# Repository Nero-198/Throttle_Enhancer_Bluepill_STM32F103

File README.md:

# Throttle Enhancer Bluepill STM32F103

## 概要
本プロジェクトは、STM32F103（Bluepill）を用いたスロットルエンハンサーのKiCad設計データです。

## 特徴
- STM32F103（Bluepill）を使用
- KiCad 9.0.3形式の設計ファイル
- ガーバーデータ同梱

HIDデバイスとして動作し、Saitek X-55 throttleにおける不便な機能・存在しない機能の追加を目的としています。

## ファイル構成
- `Throttle_Enhancer_Bluepill_STM32F103.kicad_pcb` : 基板レイアウト
- `Throttle_Enhancer_Bluepill_STM32F103.kicad_sch` : 回路図
- `Throttle_Enhancer_Bluepill_STM32F103.kicad_pro` : プロジェクトファイル
- `V1.zip` : ガーバーデータのZIPアーカイブ

## 使い方
1. KiCad 9.0.3以降でプロジェクトファイルを開く
2. 必要に応じて編集
3. `V1/`内のガーバーデータを基板製造業者に提出

## 必要なソフトウェア
- KiCad 9.0.3以降

## ライセンス
MIT

---

## STM32F103C6Tx ピン配置図

### 主なピンアサイン

| ピン名   | 機能                |
|----------|---------------------|
| PB9      | TDC_CALIBRATION     |
| PB8      | SLIDER_UP           |
| PB7      | SLIDER_HALF_UP      |
| PB6      | SLIDER_PUSH         |
| PB5      | SLIDER_HALF_DOWN    |
| PB4      | SLIDER_DOWN         |
| PA15     | SYS_JTDI            |
| PA14     | SYS_JTCK-SWCLK      |
| PA13     | SYS_JTMS-SWDIO      |
| PA12     | USB_DP              |
| PA11     | USB_DM              |
| PA10     | USART1_RX           |
| PA9      | USART1_TX           |
| PB15     | PINKY_AFT           |
| PB14     | PINKY_FWD           |
| PB13     | DOGFIGHT            |
| PB12     | MISSILE             |
| PA3      | TDC2_Y              |
| PA2      | TDC2_X              |
| PA1      | TDC_Y               |
| PA0      | TDC_X               |
| PA6      | TDC2_PUSH           |
| PA5      | TDC_PUSH            |
| PB1      | BRK_RET             |
| PB0      | BRK_EXT             |

※詳細は画像を参照してください。

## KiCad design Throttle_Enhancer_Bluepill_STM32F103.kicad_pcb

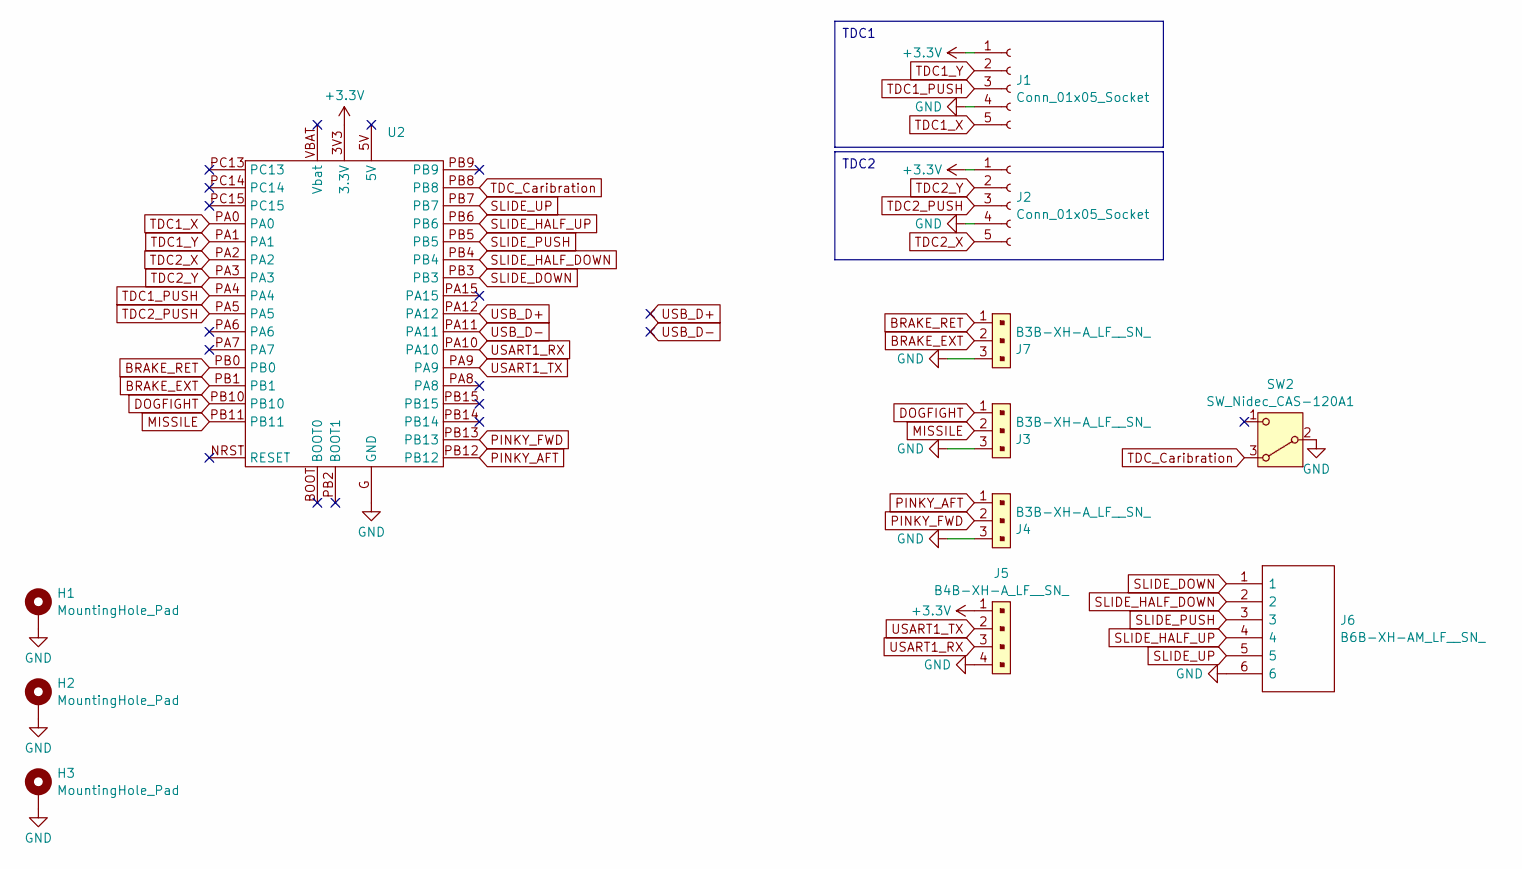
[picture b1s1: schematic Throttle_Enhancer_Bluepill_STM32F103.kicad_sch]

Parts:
H1, H2, H3: MountingHole_Pad; MountingHole_3.2mm_M3_DIN965
J1, J2: Conn_01x05_Socket; PinSocket_1x05_P2.54mm_Vertical
J3, J4, J7: B3B-XH-A_LF__SN_; PinHeader_1x3_P2.5mm_Drill1.1mm; MPN B3B-XH-A(LF)(SN); Digi-Key_PN 455-2248-ND
J5: B4B-XH-A_LF__SN_; PinHeader_1x4_P2.5mm_Drill1.1mm; MPN B4B-XH-A(LF)(SN); Digi-Key_PN 455-2249-ND
J6: B6B-XH-AM_LF__SN_; B6BXHAMLFSN; Manufacturer_Part_Number B6B-XH-AM(LF)(SN)
SW2: SW_Nidec_CAS-120A1; PinSocket_1x03_P2.54mm_Vertical
U2: blue_pill_STM32F103C6T6

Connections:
+3.3V: J1.1, J2.1, J5.1, U2.3V3 (3.3V)
BRAKE_EXT: J7.2, U2.PB1
BRAKE_RET: J7.1, U2.PB0
DOGFIGHT: J3.1, U2.PB10
GND: H1.1, H2.1, H3.1, J1.4, J2.4, J3.3, J4.3, J5.4, J6.6, J7.3, SW2.2 (B), U2.G (GND)
MISSILE: J3.2, U2.PB11
PINKY_AFT: J4.1, U2.PB12
PINKY_FWD: J4.2, U2.PB13
SLIDE_DOWN: J6.1, U2.PB3
SLIDE_HALF_DOWN: J6.2, U2.PB4
SLIDE_HALF_UP: J6.4, U2.PB6
SLIDE_PUSH: J6.3, U2.PB5
SLIDE_UP: J6.5, U2.PB7
TDC1_PUSH: J1.3, U2.PA4
TDC1_X: J1.5, U2.PA0
TDC1_Y: J1.2, U2.PA1
TDC2_PUSH: J2.3, U2.PA5
TDC2_X: J2.5, U2.PA2
TDC2_Y: J2.2, U2.PA3
TDC_Caribration: SW2.3 (A), U2.PB8
USART1_RX: J5.3, U2.PA10
USART1_TX: J5.2, U2.PA9
USB_D+: U2.PA12
USB_D-: U2.PA11

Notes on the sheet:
TDC2
TDC1

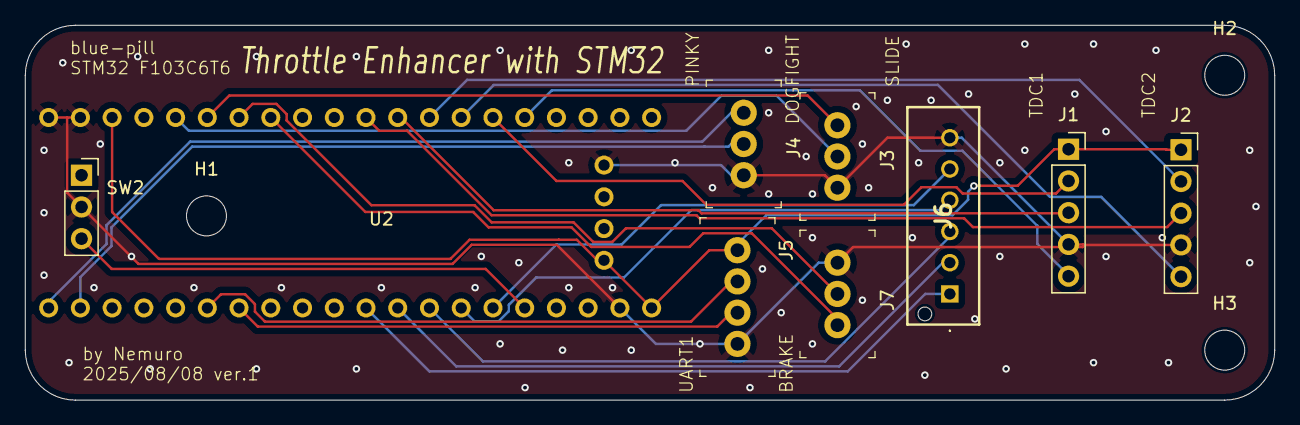
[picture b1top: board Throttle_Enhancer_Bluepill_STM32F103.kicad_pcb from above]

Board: 2 copper layers, 100.0 x 30.0 mm, 12 parts (0 on the bottom side), 22 nets.

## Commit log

2025-08-08 add logo
2025-08-08 add README.md
